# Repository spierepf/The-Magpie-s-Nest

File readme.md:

# Getting Started

1. install [pyenv](https://github.com/pyenv/pyenv/wiki#suggested-build-environment)
1. `pyenv install micropython`
1. `cd SwitchboardOperatorGame/`
1. type `python` and verify MicroPython v1.x is displayed
1. execute `python test.py` to install dependencies and verify working env

# Terminology

Net - Any connected pins, used in mock testing
Node - Representation of input on foot ball and port hole
Node Pair - A pair of portholes the game wants connected
Pair Connect - When Node pair is connected, a small visual reward for user is displayed
Pair Disconnect - When a Node pair is disconnected, nothing or negative visual is displayed
Winning - All three (or n) node pairs are connected, a grand reward is displayed to user

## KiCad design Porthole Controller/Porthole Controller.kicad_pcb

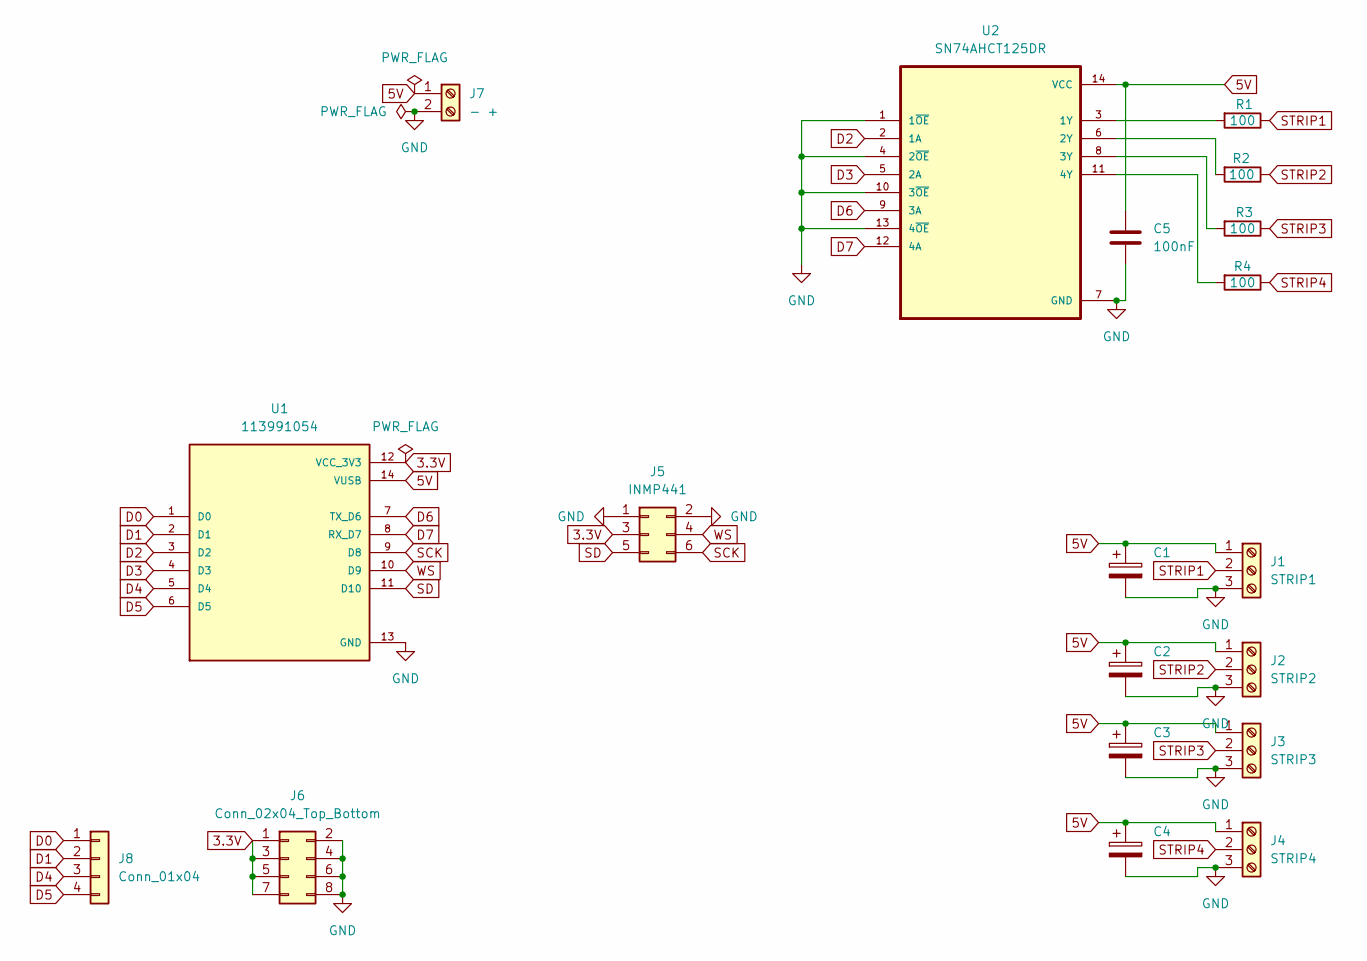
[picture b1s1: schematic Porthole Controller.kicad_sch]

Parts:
C1, C2, C3, C4: 1000uF; CP_Radial_D8.0mm_P3.80mm
C5: 100nF; C_Disc_D3.0mm_W1.6mm_P2.50mm
J1: STRIP1; TerminalBlock_bornier-3_P5.08mm
J2: STRIP2; TerminalBlock_bornier-3_P5.08mm
J3: STRIP3; TerminalBlock_bornier-3_P5.08mm
J4: STRIP4; TerminalBlock_bornier-3_P5.08mm
J5: INMP441; PinSocket_2x03_P2.54mm_Vertical
J6: Conn_02x04_Top_Bottom; PinSocket_2x04_P2.54mm_Vertical
J7: - +; TerminalBlock_bornier-2_P5.08mm
J8: Conn_01x04; PinSocket_1x04_P2.54mm_Vertical
R1, R2, R3, R4: 100; R_Axial_DIN0204_L3.6mm_D1.6mm_P5.08mm_Horizontal
U1: 113991054; xiaoesp32_c3_MM; PARTREV 23/05/2022
U2: SN74AHCT125DR; N14_TEX

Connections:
3.3V: J5.3, J6.1, J6.3, J6.5, J6.7, U1.12 (VCC_3V3)
5V: C1.1, C2.1, C3.1, C4.1, C5.1, J1.1, J2.1, J3.1, J4.1, J7.1, U1.14 (VUSB), U2.14 (VCC)
D0: J8.1, U1.1 (D0)
D1: J8.2, U1.2 (D1)
D2: U1.3 (D2), U2.2 (1A)
D3: U1.4 (D3), U2.5 (2A)
D4: J8.3, U1.5 (D4)
D5: J8.4, U1.6 (D5)
D6: U1.7 (TX_D6), U2.9 (3A)
D7: U1.8 (RX_D7), U2.12 (4A)
GND: C1.2, C2.2, C3.2, C4.2, C5.2, J1.3, J2.3, J3.3, J4.3, J5.1, J5.2, J6.2, J6.4, J6.6, J6.8, J7.2, U1.13 (GND), U2.1 (1~OE), U2.4 (2~OE), U2.7 (GND), U2.10 (3~OE), U2.13 (4~OE)
unnamed: R1.2, U2.3 (1Y)
unnamed: R2.2, U2.6 (2Y)
unnamed: R3.2, U2.8 (3Y)
unnamed: R4.2, U2.11 (4Y)
SCK: J5.6, U1.9 (D8)
SD: J5.5, U1.11 (D10)
STRIP1: J1.2, R1.1
STRIP2: J2.2, R2.1
STRIP3: J3.2, R3.1
STRIP4: J4.2, R4.1
WS: J5.4, U1.10 (D9)

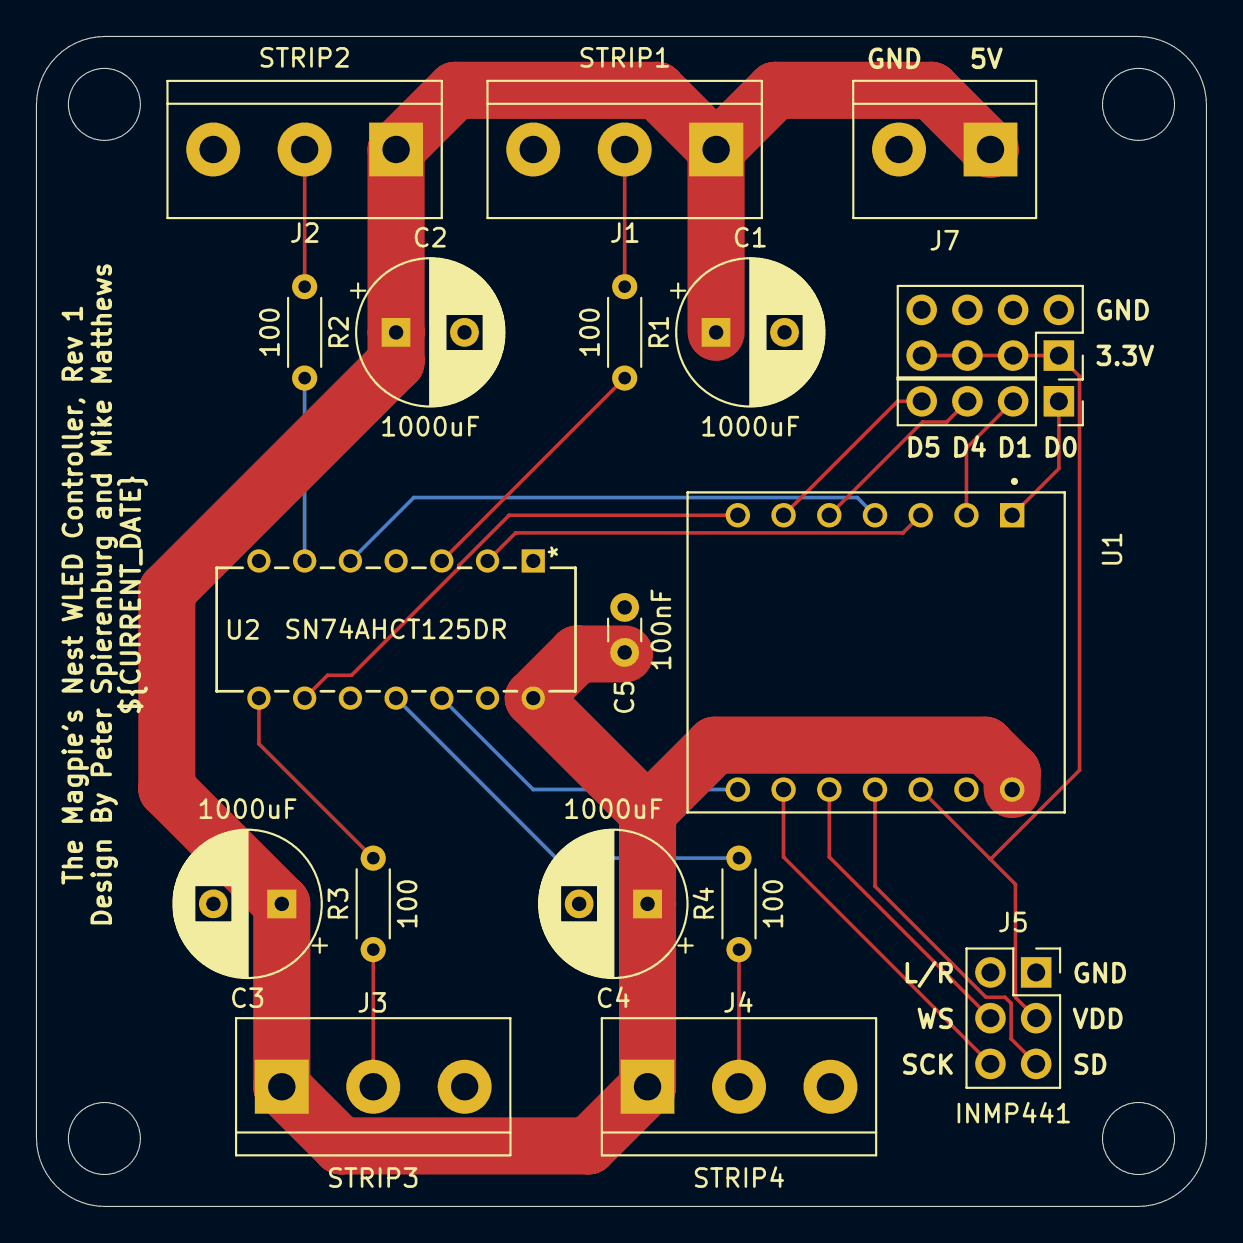
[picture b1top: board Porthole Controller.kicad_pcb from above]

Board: 2 copper layers, 65.0 x 65.0 mm, 19 parts (0 on the bottom side), 22 nets.

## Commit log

2024-05-22 Added Porthole Controller board
2024-05-22 add symbols for c3 and level shifter
2024-05-22 Added parts and most of the nets
2024-06-01 Completed schematic
2024-06-01 Added throughhole non inverting buffer
2024-06-01 Prototype board designed
2024-06-01 Added Rev 1 Gerber Files for PCB order
2024-06-02 Updated footprints
2024-06-02 Updated .gitignore
2024-06-02 Added Ryan's Damask to back silkscreen
2024-06-02 Added silkscreen for INMP441 pinout
2024-06-02 Added variables to silkscreen for revision number and date
2024-06-02 Added pinout symbol
2024-06-02 Added pinout table to pcb
2024-06-02 bolden text, fix capacitor labels, reviewed DRC warnings
2024-09-25 Added SwitchboardOperatorGame
2025-04-07 Too much stuff
2025-07-06 Added unittest.mock to test.py
2025-07-06 Added NodePair class
2025-07-06 Add AI generated simulator for switchboard game, setup readme, and game_ideas readme
2025-07-06 Replaced local Observable class with implementation from upatterns
2025-07-06 Extracted mock pin code to umockpin package
2025-07-06 Basic visualization for magpie simulator
2025-07-06 Renamed NodePair::check to poll
2025-07-06 simulator now reacts to wled state color and pride fx
2025-07-07 Allow front and back to be controlled individually by segment 0 and 1
2025-07-09 move references to mip_packages
2025-07-17 linting, mDNS advertising fix
2025-07-17 Replace ulogging package with logging
2025-07-17 Added GameController and tests
2025-07-17 Updated test_Send to confirm mdns advertising is working
2025-07-17 fixed test send to get port from mdns
2025-07-18 Added Node::__repr__
2025-07-18 Added NodePair::__repr__
2025-07-18 Added logging to GameController
2025-07-18 Reset main.py
2025-07-19 Added pair logging to GameController
2025-07-19 Can run tests directly in PyCharm
2025-07-19 NodePairs reveal their connection state through the poll() method and not observavble
2025-07-19 "Vibe Coded" Framework for Micropython scoreboard Game
2025-07-19 Removed unused members of Node class
2025-07-19 NodePairs can now give hints
2025-07-20 Added hinting
2025-07-22 Add support for extra wled endpoints and per segment effect
2025-07-23 Added logging to node_pair
2025-07-23 Added aux to node
2025-07-23 Added Sequencer class and tests
2025-07-27 Removed semicolon
2025-07-29 Added ESP8266 Magpie Control
2025-07-29 Merge (#1)
    * Added ESP8266 Magpie Control
    * Delete ESP8266 Magpie Control/include/secrets.hpp
    * Update .gitignore
2025-07-31 Using correct effect index for Pride 2015
2025-07-31 mdns advertisement improvements
2025-07-31 Support Solid effect
2025-07-31 Added uv goodness to MagpieSimulator
2025-08-03 Improved ESP8266 Magpie Control
2025-10-11 Changed signature of Sequencer.after
2025-10-11 NodePairs can confirm when their connection has been made
2025-10-15 Basic gameplay
2025-10-17 Final preparation
2025-12-29 Added seedling of BlackAndWhiteNoise
2026-01-03 Reinitializing BlackAndWhiteNoise
2026-01-03 Added infrastructure
2026-01-03 Added ub.lock
2026-01-03 Implemented basic autoupdate service
2026-01-04 Added ESP32Station
2026-01-05 Added Serial
2026-01-05 Added wifi
